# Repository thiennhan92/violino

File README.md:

# VIOLINO
Violino is an open hard-ware project. Created form iMX233-OLinuXino-MAXI SINGLE-BOARD COMPUTER schematic
https://www.olimex.com/Products/OLinuXino/iMX233/iMX233-OLinuXino-MAXI/open-source-hardware

Ho Chi Minh City - August 2018
# Target
* Building a Single-Board Computer
* Learn about the U-Boot bootloader and the Yocto Project
# Board Description

* iMX233 ARM926J processor at 454Mhz
* 64 MB RAM
* SD-card connector for booting the Linux image
* TV PAL/NTSC video output
* 1 micro USB connect with iMX233 IC
* 2 USB High Speed Hosts
* Ethernet 10/100 Mbit
* Two buttons
* Two led power
* 44 pin GPIO for connection of other hardware
* Power supply input 5VDC, min current 1.5A
* 4 layer FR-4 PCB
* PCB dimensions: 3.54'' x 1.97'' (90.0mm x 50.0mm)

# 3D VIEW

# PCB BOARD

#FIST BOOT

#LCD

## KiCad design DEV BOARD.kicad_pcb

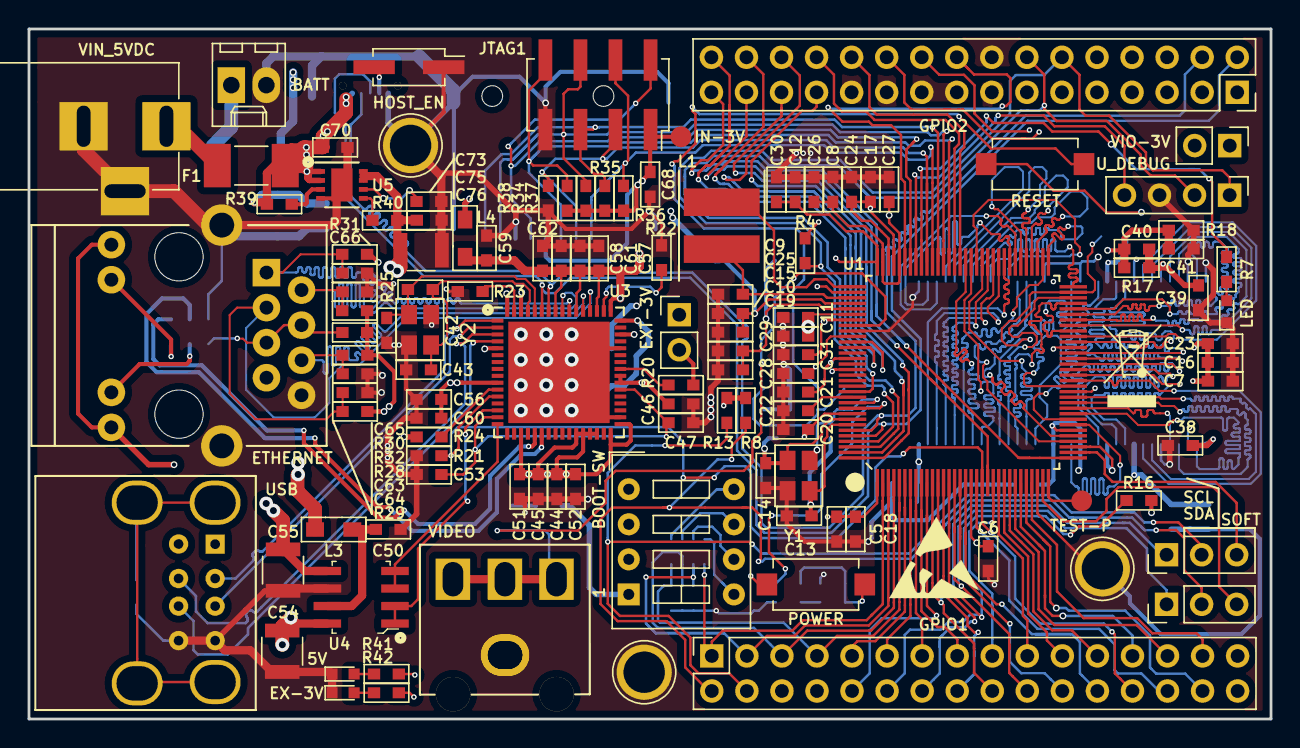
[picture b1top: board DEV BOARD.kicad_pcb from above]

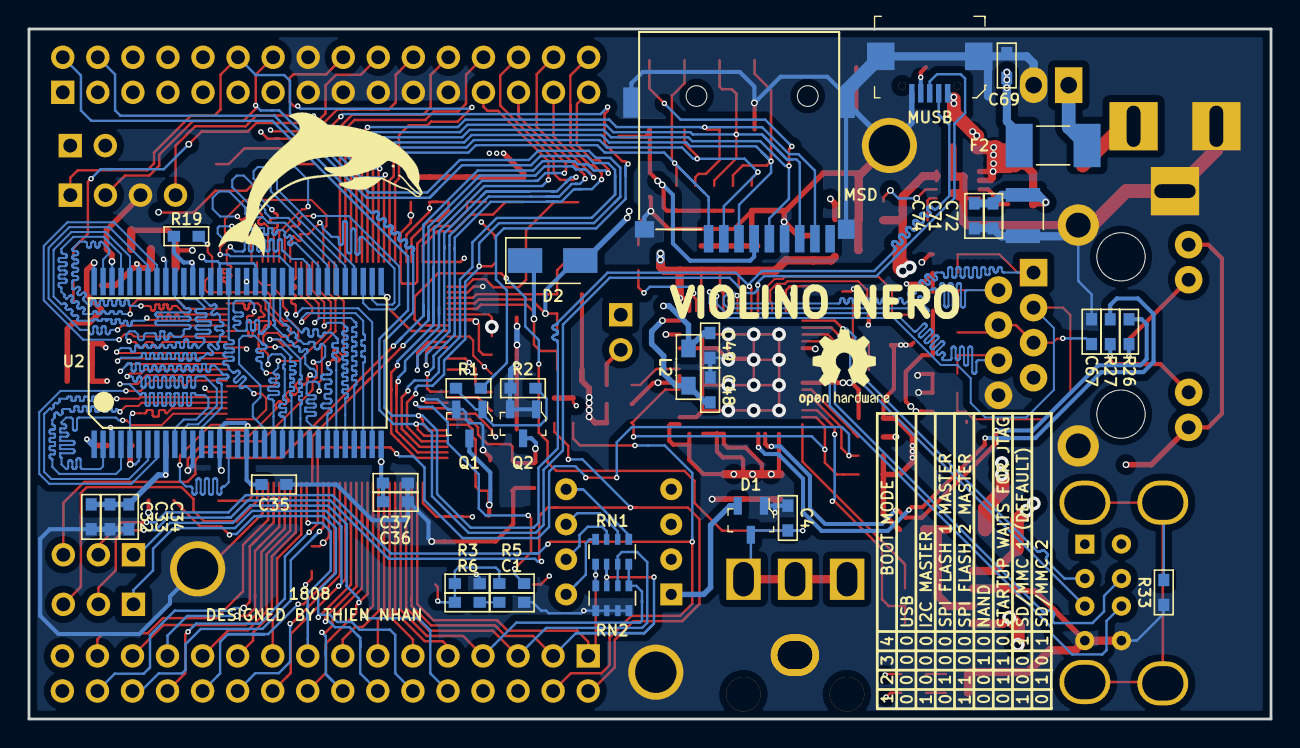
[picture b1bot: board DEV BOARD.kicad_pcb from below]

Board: 4 copper layers, 90.0 x 50.0 mm, 153 parts (35 on the bottom side), 160 nets.

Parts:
5V: LED; LED_0603
BATT: Conn_01x02; Molex_KK-6410-02_02x2.54mm_Straight
BOOT-SW: DIPSW04_SMD; SW_DIP_x4_W7.62mm_Slide
C1, C11, C12, C16, C20, C21, C23, C24, C32, C33, C34, C35, C36, C37, C38, C39, C40, C41, C44, C45, C46, C47, C48, C51, C52, C53, C56, C57, C58, C59, C60, C61, C62, C71, C74, C75: C0603/100nF; 0603_HandSoldering
C4: C0603/47pF; 0603_HandSoldering
C5, C6, C7, C8, C10, C15, C17, C18, C19, C25, C26, C27, C28, C29, C30, C31, C68, C69: C0603/22uF/6.3V; 0603_HandSoldering
C9: C0603/10pF; 0603_HandSoldering
C13, C14, C42, C43: C0603/33pF; 0603_HandSoldering
C22: C0603/1uF; 0603_HandSoldering
C49: C0603/4.7uF; 0603_HandSoldering
C50: C0603/10uF; 0603_HandSoldering
C54, C55, C72, C76: C1210/100uF/6.3V; C_1210
C63, C64, C65, C66, C67: C0603/15pF; 0603_HandSoldering
C70: C0603/4.7nF; 0603_HandSoldering
C73: C0603/1nF; 0603_HandSoldering
D1: BAT54S-7-F; SOT-23-3
D2: SS14; D_SMA
ETHERNET: RJ45-HR911105A; RJ45_HR911105A
EX-3V: LED; LED_0603
EXT-3V: Jumper_NC; Socket_Strip_Straight_1x02_Pitch2.54mm
F1: MINISMDC250F/16V; Fuse_0679H
F2: MF-MSMF050; Fuse_0679H
GPIO1, GPIO2: Conn_02x16_Odd_Even; Socket_Strip_Straight_2x16_Pitch2.54mm
HOST_EN: Con_1x2_SMD; Socket_Strip_Straight_2x01_Pitch2.54mm_SMD
IN-3V: TEST_1P; Measurement_Point_Round-SMD-Pad_Small
JTAG1: Conn_02x04_Odd_Even; Socket_Strip_Straight_2x04_Pitch2.54mm_SMD
L1: L_22uH/1.A(CD53-220); CD53_SERIES_HandSoldering
L2, L3, L4: FBMH2012HM121-T; 0805_HandSoldering
LED: LED; LED_0603
MSD: 9P-MSD-PP-V2; MicroSD_9Pin_MSD-PP-V2
MUSB: USB_OTG; USB_Micro_B_Female_SMD
POWER: GPTS203211B; SW_3x6x5_2Pin_SMD
Q1, Q2: BC846B_215; SOT-23-3
R1, R2, R16: R0603/47K; 0603_HandSoldering
R3, R4: R0603/100K; 0603_HandSoldering
R5, R6: R0603/1K; 0603_HandSoldering
R7, R42: R0603/100R; 0603_HandSoldering
R8, R13: R0603/2K2; 0603_HandSoldering
R17, R18: R0603/1K/1%; 0603_HandSoldering
R19, R20, R21, R24, R34, R38, R40: R0603/10K; 0603_HandSoldering
R22: R0603/12K4/1%; 0603_HandSoldering
R23: R0603/12K/1%; 0603_HandSoldering
R25, R37: R0603/1M; 0603_HandSoldering
R26, R27: R0603/560R; 0603_HandSoldering
R28, R29, R30, R31: R0603/49R9/1%; 0603_HandSoldering
R32: R0603/10R/1%; 0603_HandSoldering
R33: R0603/560R/1%; 0603_HandSoldering
R35, R36: R0603 10K; 0603_HandSoldering
R39: R0603/10R; 0603_HandSoldering
R41: R0603/330R; 0603_HandSoldering
RESET: GPTS203211B; SW_3x6x5_2Pin_SMD
RN1, RN2: R_Pack04; R_Array_Convex_4x0603
SCL: Conn_01x03_Male; Socket_Strip_Straight_1x03_Pitch2.54mm
SDA: Conn_01x03_Male; Socket_Strip_Straight_1x03_Pitch2.54mm
TEST-P: TEST_1P; Measurement_Point_Round-SMD-Pad_Small
U1: MCIMX233CAG4C; QFP_128
U2: HY5DU121622DTP; HY5DU121622D(L)TP_TSOP-66
U3: LAN9512-JZX; QFN-64-1EP_9x9mm_Pitch0.5mm
U4: MIC2026-1YM-TR; SOIC-8_W3.9mm
U5: MCP1727; DFN-8-1EP_3x3mm_Pitch0.65mm
USB: DUAL_USB_TYPE_A; DUAL_USB_FEMALE_TYPE_A
U_DEBUG: Conn_01x04; Socket_Strip_Straight_1x04_Pitch2.54mm
VIDEO: Conn_Coaxial; RCA_CONNECTOR_1PIN
VIN_5VDC: Jack-DC; BARREL_JACK
VIO-3V: Jumper_NO; Socket_Strip_Straight_1x02_Pitch2.54mm
Y1: Crystal_24MHz; Crystal_SMD_SeikoEpson_TSX3225-4pin_3.2x2.5mm_HandSoldering
Y2: Crystal_25MHz; Crystal_SMD_SeikoEpson_TSX3225-4pin_3.2x2.5mm_HandSoldering

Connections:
2V5: C7.1, C16.1, C23.1, C28.1, C32.1, C33.1, C34.1, C35.1, C36.1, C37.1, C38.1, C39.1, C40.1, R17.1, R19.1, U1.38, U1.45, U1.53, U1.106, U2.1, U2.3, U2.9, U2.15, U2.18, U2.33, U2.55, U2.61
3.3VIO: BOOT-SW.1, BOOT-SW.2, BOOT-SW.3, BOOT-SW.4, C6.1, C8.1, C26.1, C27.1, C68.1, D1.2, IN-3V.1, JTAG1.1, MSD.4, R4.1, R8.1, R13.1, R16.1, R34.1, R35.1, R36.1, R38.1, RESET.1, U1.18, U1.92, U1.95, VIO-3V.2
3V3: C44.1, C45.1, C46.1, C51.1, C52.1, ETHERNET.9, ETHERNET.12, EXT-3V.2, GPIO2.1, GPIO2.3, L4.1, R20.2, R24.2, R42.2, U3.19, U3.27, U3.28, U3.29, U3.30, U3.32, U3.33, U3.39, U3.40, U3.46, VIO-3V.1
5V: C11.1, C29.1, C70.1, C71.1, C72.1, C74.1, F1.1, GPIO2.5, GPIO2.7, L3.1, MUSB.1, R39.1, R41.2, U1.102, U5.1, U5.2
/ARM_CPU/DCDC_VDDA: C12.1, C21.1, C30.1, U1.96, U1.110
/ARM_CPU/DCDC_VDDD: C5.1, C17.1, C18.1, C24.1, U1.1, U1.93, U1.94
/ARM_CPU/RESET: R1.2, RESET.2
/ARM_CPU/SJTAG_PSW: POWER.2, R3.1, R5.1, R6.1
/ARM_CPU/VDDXTAL: C20.1, POWER.1, U1.120
/ARM_CPU/XTI: C13.1, Q1.3, U1.122, Y1.1
/ARM_CPU/XTO: C14.1, Q2.3, U1.121, Y1.3
/USB-ETHERNET CONTROLLER/AVCC: C56.2, C57.2, C58.2, C59.2, C60.2, C61.2, C62.2, L4.2, R28.2, R29.2, R30.2, R31.2, R32.2, U3.5, U3.10, U3.49, U3.51, U3.54, U3.57, U3.64
/USB-ETHERNET CONTROLLER/PRTCTL2: U3.14, U4.1, U4.2
/USB-ETHERNET CONTROLLER/PRTCTL3: U3.16, U4.3, U4.4
/USB-ETHERNET CONTROLLER/RX+: C64.2, ETHERNET.3, R29.1, U3.52
/USB-ETHERNET CONTROLLER/RX-: C63.2, ETHERNET.6, R28.1, U3.53
/USB-ETHERNET CONTROLLER/TX+: C66.2, ETHERNET.1, R31.1, U3.55
/USB-ETHERNET CONTROLLER/TX-: C65.2, ETHERNET.2, R30.1, U3.56
/USB-ETHERNET CONTROLLER/USB2_N: U3.1, USB.2
/USB-ETHERNET CONTROLLER/USB2_P: U3.2, USB.3
/USB-ETHERNET CONTROLLER/USB3_N: U3.3, USB.6
/USB-ETHERNET CONTROLLER/USB3_P: U3.4, USB.7
/USB-ETHERNET CONTROLLER/USB_PWR_2: C54.2, U4.8, USB.1
/USB-ETHERNET CONTROLLER/USB_PWR_3: C55.2, U4.5, USB.5
A00: U1.76, U2.29
A01: U1.75, U2.30
A02: U1.74, U2.31
A03: U1.73, U2.32
A04: U1.72, U2.35
A05: U1.71, U2.36
A06: U1.70, U2.37
A07: U1.69, U2.38
A08: U1.68, U2.39
A09: U1.67, U2.40
A10: U1.66, U2.28
A11: U1.65, U2.41
A12: U1.64, U2.42
AUART1_RDX: GPIO2.27, U1.128
AUART1_TXD: GPIO2.25, U1.127
BA0: U1.79, U2.26
BA1: U1.80, U2.27
BATT+: C15.1, C25.1, C31.1, C69.1, D2.2, F2.2, GPIO2.13, U1.100, U1.103
CASN: U1.61, U2.22
CKE: U1.78, U2.44
CLK: U1.36, U2.45
CLKN: U1.37, U2.46
CS: R19.2, U1.63, U2.24
D00: U1.41, U2.2
D01: U1.43, U2.4
D02: U1.42, U2.5
D03: U1.44, U2.7
D04: U1.47, U2.8
D05: U1.48, U2.10
D06: U1.49, U2.11
D07: U1.50, U2.13
D08: U1.51, U2.54
D09: U1.52, U2.56
D10: U1.54, U2.57
D11: U1.55, U2.59
D12: U1.57, U2.60
D13: U1.58, U2.62
D14: U1.60, U2.63
D15: U1.59, U2.65
DEBUG: U1.89, U_DEBUG.4
DQM0: U1.46, U2.20
DQM1: U1.56, U2.47
DQS0: U1.39, U2.16
DQS1: U1.40, U2.51
GND: 5V.1, BATT.2, C1.2, C4.2, C5.2, C6.2, C7.2, C8.2, C9.2, C10.2, C11.2, C12.2, C13.2, C14.2, C15.2, C16.2, C17.2, C18.2, C19.2, C20.2, C21.2, C22.2, C23.2, C24.2, C25.2, C26.2, C27.2, C28.2, C29.2, C30.2, C31.2, C32.2, C33.2, C34.2, C35.2, C36.2, C37.2, C38.2, C39.2, C41.2, C42.2, C43.2, C44.2, C45.2, C46.2, C47.2, C48.2, C49.2, C50.1, C51.2, C52.2, C53.2, C54.1, C55.1, C56.1, C57.1, C58.1, C59.1, C60.1, C61.1, C62.1, C63.1, C64.1, C65.1, C66.1, C67.1, C68.2, C69.2, C70.2, C71.2, C72.2, C73.2, C74.2, C75.2, C76.2, D1.1, ETHERNET.8, ETHERNET.13, EX-3V.1, GPIO2.15, GPIO2.16, GPIO2.17, GPIO2.19, GPIO2.21, GPIO2.23, HOST_EN.1, JTAG1.7, LED.1, MSD.6, MSD.10, MUSB.5, MUSB.6, Q1.2, Q2.1, Q2.2, R2.2, R3.2, R18.2, R21.2, R22.2, R23.2, R33.1, R37.2, RN2.5, RN2.6, RN2.7, RN2.8, U1.30, U1.35, U1.98, U1.105, U1.112, U1.118, U2.6, U2.12, U2.34, U2.48, U2.52, U2.58, U2.64, U2.66, U3.34, U3.44, U3.65, U4.6, U5.4, USB.4, USB.8, U_DEBUG.3, VIDEO.2, VIN_5VDC.2, VIN_5VDC.3, Y1.2, Y1.4, Y2.2, Y2.4
I2C_SCL: GPIO1.4, R13.2, SCL.2
I2C_SDA: GPIO1.2, R8.2, SDA.2
LED1: R7.2, U1.88
unnamed: 5V.2, R41.1
unnamed: BATT.1, F2.1
unnamed: C1.1, R6.2
unnamed: C9.1, L1.2, U1.99
unnamed: C10.1, C19.1, D2.1, U1.101
unnamed: C22.1, U1.117
unnamed: C40.2, C41.1, R17.2, R18.1, U2.49
unnamed: C42.1, R25.2, U3.60, Y2.1
unnamed: C43.1, R25.1, U3.61, Y2.3
unnamed: C47.1, C53.1, U3.15, U3.38
unnamed: C48.1, L2.2, U3.48
unnamed: C49.1, L2.1, U3.62
unnamed: C50.2, L3.2, U4.7
unnamed: C67.2, ETHERNET.4, ETHERNET.5, R32.1
unnamed: C73.1, U5.6
unnamed: C75.1, C76.1, EXT-3V.1, R40.1, U5.7, U5.8
unnamed: EX-3V.2, R42.1
unnamed: HOST_EN.2, MUSB.4
unnamed: TEST-P.1, U1.32
unnamed: ETHERNET.10, R26.1
unnamed: ETHERNET.11, R27.1
unnamed: L1.1, U1.97
unnamed: LED.2, R7.1
unnamed: Q1.1, R1.1, R2.1
unnamed: R20.1, U3.41
unnamed: R22.1, U3.50
unnamed: R23.1, U3.63
unnamed: R24.1, U3.11
unnamed: R26.2, U3.21
unnamed: R27.2, U3.22
unnamed: R33.2, USB.9, USB.10, USB.11, USB.12
unnamed: R39.2, U5.3
unnamed: R40.2, U5.5
unnamed: BOOT-SW.8, RN1.1
unnamed: BOOT-SW.7, RN1.2
unnamed: BOOT-SW.6, RN1.3
unnamed: BOOT-SW.5, RN1.4
PIN1/LCD_D00: GPIO1.1, RN1.5, RN2.4, U1.2
PIN2/LCD_D01: GPIO1.3, RN1.6, RN2.3, U1.3
PIN3/LCD_D02: GPIO1.5, RN1.7, RN2.2, U1.4
PIN4/LCD_D03: GPIO1.7, RN1.8, RN2.1, U1.5
PIN5/LCD_D04: GPIO1.9, U1.6
PIN6/LCD_D05: GPIO1.11, U1.7
PIN7/LCD_D06: GPIO1.13, U1.8
PIN8/LCD_D07: GPIO1.15, U1.9
PIN9/LCD_D08/SSP2_MISO: GPIO1.17, U1.22
PIN10/LCD_09: GPIO1.19, U1.23
PIN11/LCD_D10: GPIO1.21, U1.24
PIN12/LCD_D11: GPIO1.23, U1.25
PIN13/LCD_D12: GPIO1.25, U1.27
PIN14/LCD_D13: GPIO1.27, U1.26
PIN15/LCD_D14: GPIO1.29, U1.29
PIN16/LCD_D15: GPIO1.30, U1.28
PIN17/LCD_D16: GPIO1.28, U1.19
PIN18/LCD_D17/USB_EN: GPIO1.26, R21.1, U1.20, U3.12
PIN19/LCD_DOTCLK: GPIO1.24, U1.17
PIN20/LCD_VSYNC: GPIO1.22, U1.16
PIN21/LCD_HSYNC/I2C_SDA: GPIO1.20, SDA.1, U1.15
PIN22/LCD_EN/I2C_SCL: GPIO1.18, SCL.1, U1.11
PIN23/LCD_DISP: GPIO1.16, U1.12
PIN24/LCD_WR: GPIO1.14, U1.13
PIN25/LCD_RS: GPIO1.12, R16.2, U1.14
PIN26/LCD_CS: GPIO1.10, U1.10
PIN27/PWM2: GPIO2.18, U1.91
PIN28/SOFT_SDA: GPIO2.20, SDA.3, U1.31
PIN29/SOFT_SCL: GPIO2.22, SCL.3, U1.34
PIN30: GPIO2.24, U1.81
PIN31: GPIO2.26, U1.82
PIN32/LRADC1: GPIO2.28, U1.107
PIN33/LRADC0: GPIO2.30, U1.108
PIN34/MIC: GPIO2.32, U1.116
PWM0/DUART_RXD: GPIO2.12, R4.2, U1.125, U_DEBUG.1
PWM1/DUART_TXD: GPIO2.14, U1.126, U_DEBUG.2
P_SWITCH: R5.2, U1.119
RASN: U1.62, U2.23
SSP1_CMD: JTAG1.8, MSD.3, R38.2, U1.83
SSP1_DATA0: JTAG1.6, MSD.7, R34.2, U1.84
SSP1_DATA1: JTAG1.5, MSD.8, R35.2, U1.85
SSP1_DATA2: JTAG1.4, MSD.1, R36.2, U1.86
SSP1_DATA3: JTAG1.3, MSD.2, R37.1, U1.87
SSP1_SCK: JTAG1.2, MSD.5, U1.90
SSP2_MOSI: GPIO2.29, U1.21
SSP2_SCK: GPIO2.31, U1.33
USB_N: GPIO2.4, MUSB.2, U1.123, U3.58
USB_P: GPIO2.2, MUSB.3, U1.124, U3.59
VIDEO: C4.1, D1.3, U1.104, VIDEO.1
V_IN: F1.2, GPIO2.9, GPIO2.11, VIN_5VDC.1
WEN: U1.77, U2.21

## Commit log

2018-08-29 update files
2018-08-29 add readme
2018-09-12 update board image"
2018-09-12 update pcb board image
2018-10-09 update booting image
2019-01-18 update gerber file
